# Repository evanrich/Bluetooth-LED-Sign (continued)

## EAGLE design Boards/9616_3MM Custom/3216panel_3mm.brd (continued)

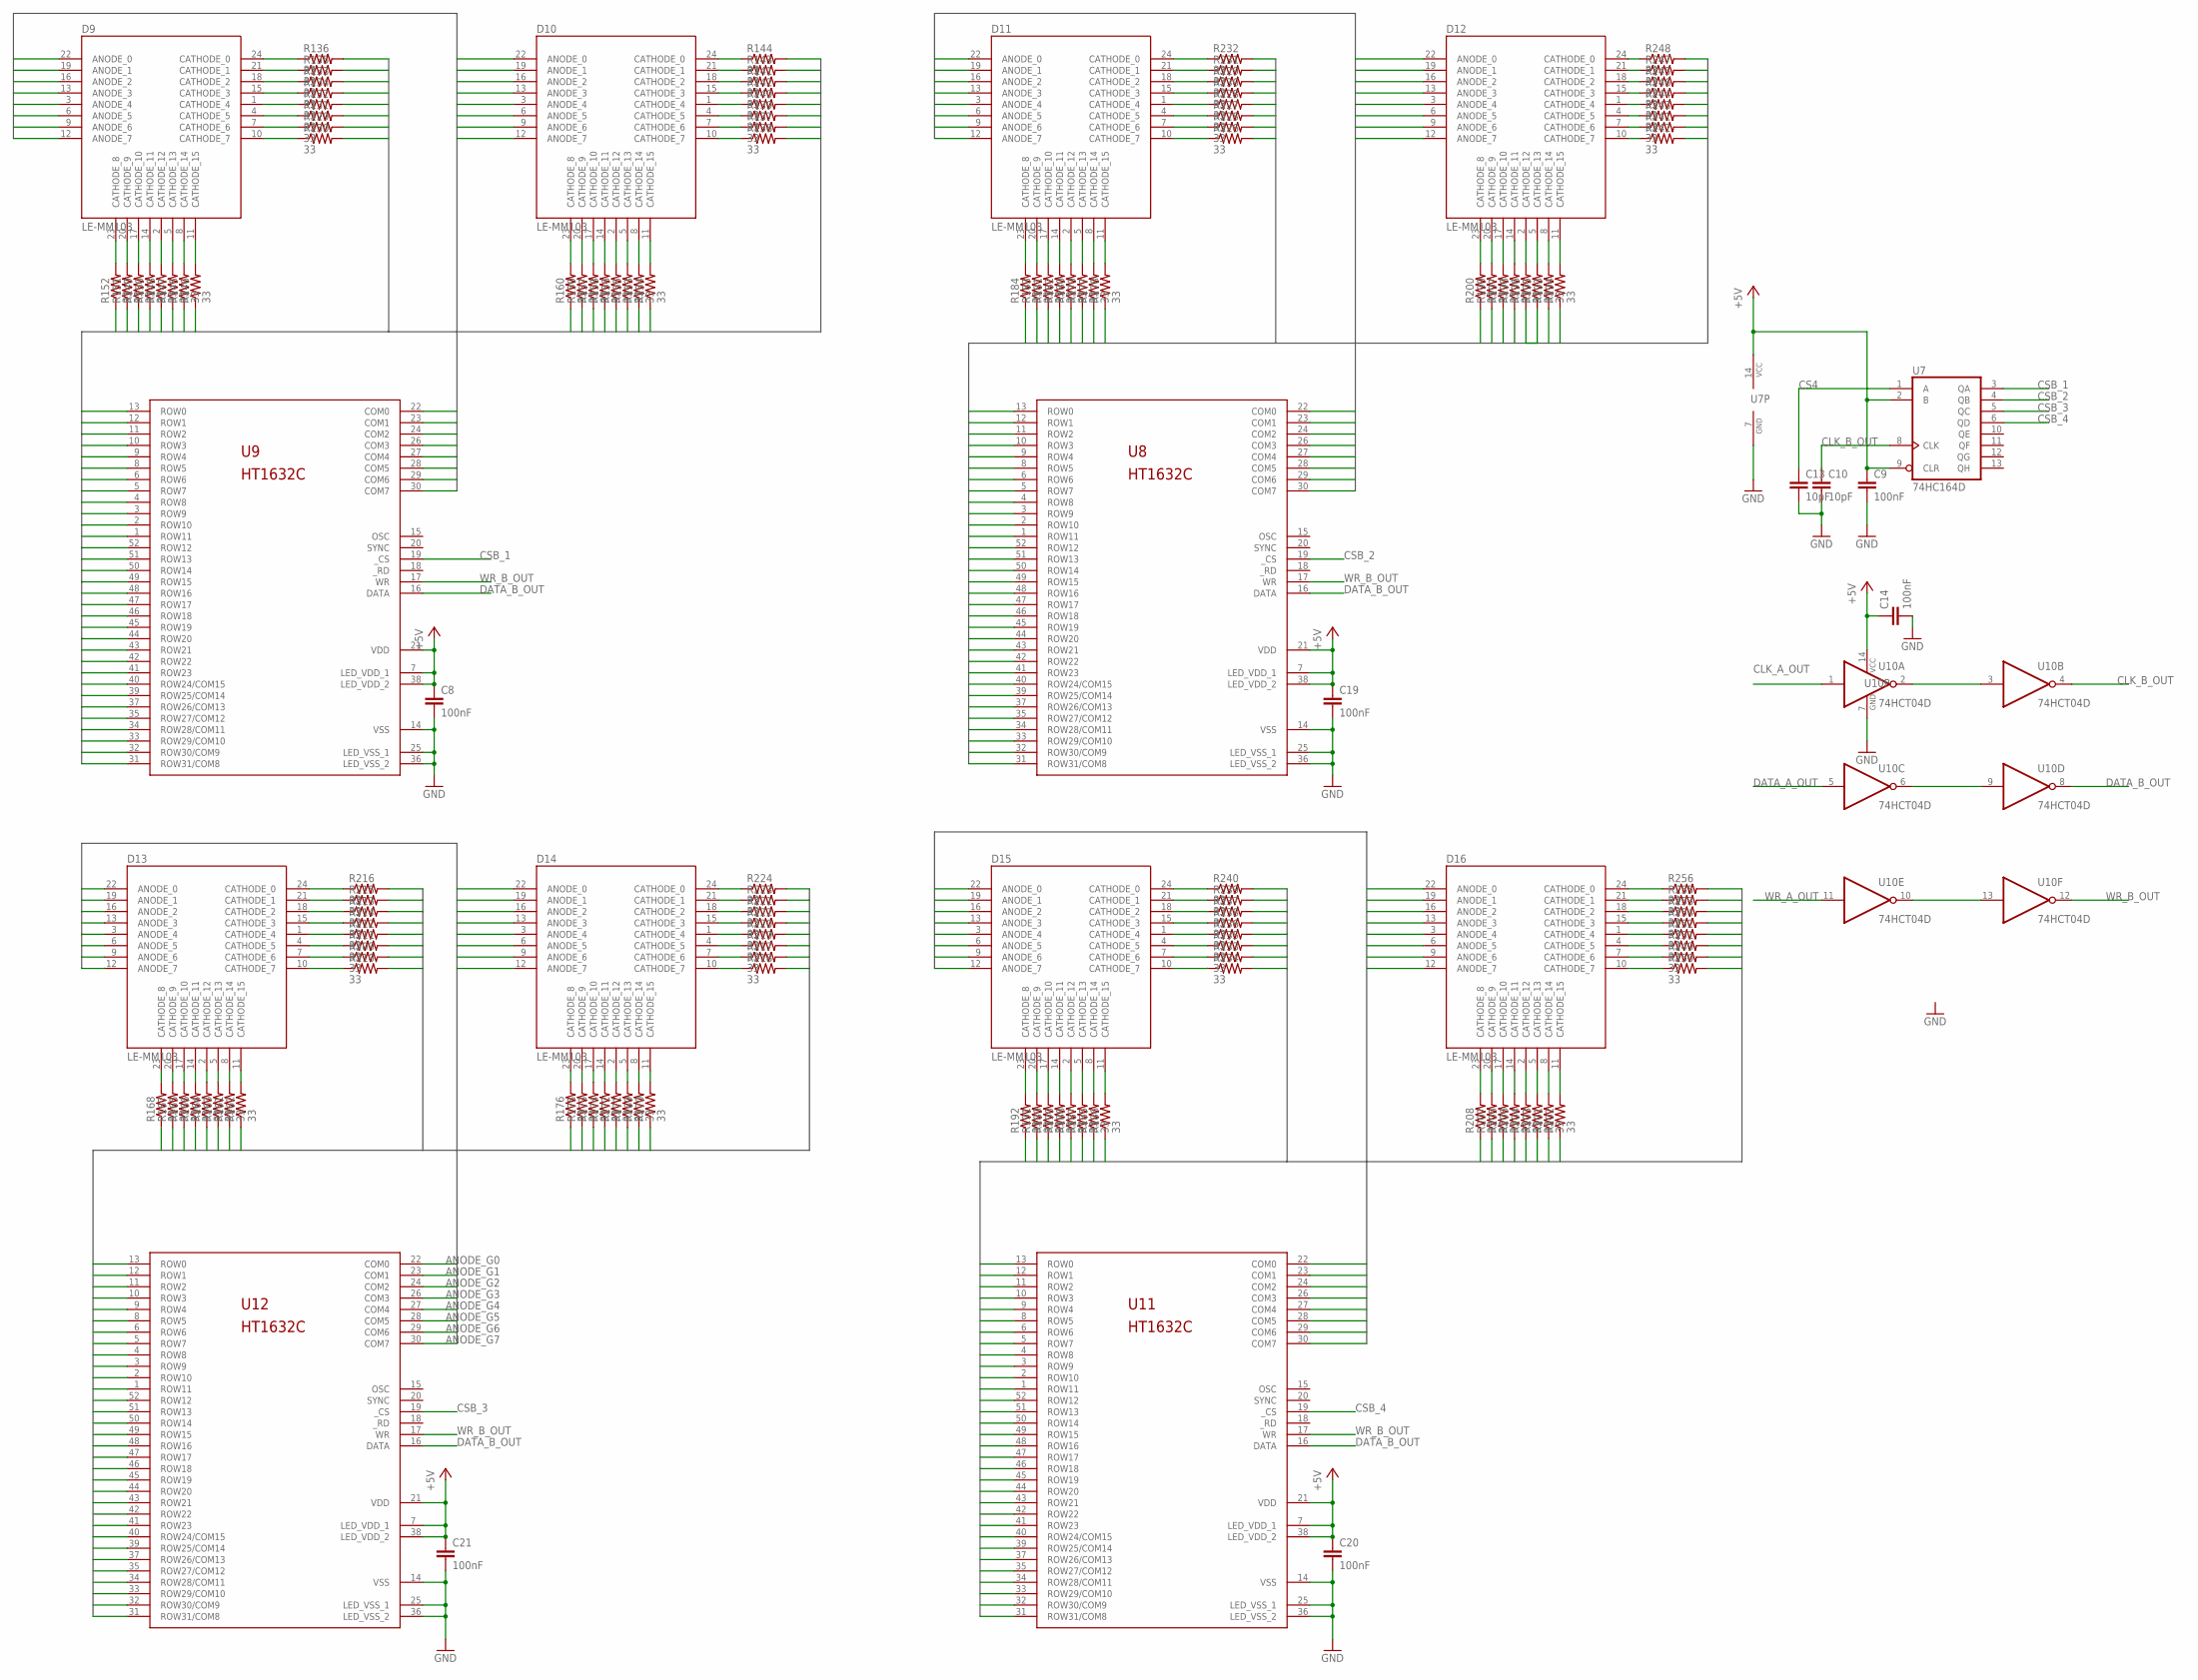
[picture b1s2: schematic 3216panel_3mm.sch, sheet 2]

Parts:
C8, C9, C14, C19, C20, C21: 100nF; 0805
C10, C13: 10pF; 0805
D9, D10, D11, D12, D13, D14, D15, D16: LE-MM103; 8X8_3MM_LED_MATRIX
R129, R130, R131, R132, R133, R134, R135, R136, R137, R138, R139, R140, R141, R142, R143, R144, R145, R146, R147, R148, R149, R150, R151, R152, R153, R154, R155, R156, R157, R158, R159, R160, R161, R162, R163, R164, R165, R166, R167, R168, R169, R170, R171, R172, R173, R174, R175, R176, R177, R178, R179, R180, R181, R182, R183, R184, R185, R186, R187, R188, R189, R190, R191, R192, R193, R194, R195, R196, R197, R198, R199, R200, R201, R202, R203, R204, R205, R206, R207, R208, R209, R210, R211, R212, R213, R214, R215, R216, R217, R218, R219, R220, R221, R222, R223, R224, R225, R226, R227, R228, R229, R230, R231, R232, R233, R234, R235, R236, R237, R238, R239, R240, R241, R242, R243, R244, R245, R246, R247, R248, R249, R250, R251, R252, R253, R254, R255, R256: 33; 0805
U7: 74HC164D; SO14
U8, U9, U11, U12: HT1632C; QFP52
U10: 74HCT04D; SO14

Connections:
+5V: C8.1, C9.1, C14.1, C19.1, C20.1, C21.1, U7.2 (B), U7.9 (CLR), U7.14 (VCC), U8.7 (LED_VDD_1), U8.21 (VDD), U8.38 (LED_VDD_2), U9.7 (LED_VDD_1), U9.21 (VDD), U9.38 (LED_VDD_2), U10.14 (VCC), U11.7 (LED_VDD_1), U11.21 (VDD), U11.38 (LED_VDD_2), U12.7 (LED_VDD_1), U12.21 (VDD), U12.38 (LED_VDD_2); also elsewhere on the board
ANODE_E0: D9.22 (ANODE_0), D10.22 (ANODE_0), U9.22 (COM0)
ANODE_E1: D9.19 (ANODE_1), D10.19 (ANODE_1), U9.23 (COM1)
ANODE_E2: D9.16 (ANODE_2), D10.16 (ANODE_2), U9.24 (COM2)
ANODE_E3: D9.13 (ANODE_3), D10.13 (ANODE_3), U9.26 (COM3)
ANODE_E4: D9.3 (ANODE_4), D10.3 (ANODE_4), U9.27 (COM4)
ANODE_E5: D9.6 (ANODE_5), D10.6 (ANODE_5), U9.28 (COM5)
ANODE_E6: D9.9 (ANODE_6), D10.9 (ANODE_6), U9.29 (COM6)
ANODE_E7: D9.12 (ANODE_7), D10.12 (ANODE_7), U9.30 (COM7)
ANODE_F0: D11.22 (ANODE_0), D12.22 (ANODE_0), U8.22 (COM0)
ANODE_F1: D11.19 (ANODE_1), D12.19 (ANODE_1), U8.23 (COM1)
ANODE_F2: D11.16 (ANODE_2), D12.16 (ANODE_2), U8.24 (COM2)
ANODE_F3: D11.13 (ANODE_3), D12.13 (ANODE_3), U8.26 (COM3)
ANODE_F4: D11.3 (ANODE_4), D12.3 (ANODE_4), U8.27 (COM4)
ANODE_F5: D11.6 (ANODE_5), D12.6 (ANODE_5), U8.28 (COM5)
ANODE_F6: D11.9 (ANODE_6), D12.9 (ANODE_6), U8.29 (COM6)
ANODE_F7: D11.12 (ANODE_7), D12.12 (ANODE_7), U8.30 (COM7)
ANODE_G0: D13.22 (ANODE_0), D14.22 (ANODE_0), U12.22 (COM0)
ANODE_G1: D13.19 (ANODE_1), D14.19 (ANODE_1), U12.23 (COM1)
ANODE_G2: D13.16 (ANODE_2), D14.16 (ANODE_2), U12.24 (COM2)
ANODE_G3: D13.13 (ANODE_3), D14.13 (ANODE_3), U12.26 (COM3)
ANODE_G4: D13.3 (ANODE_4), D14.3 (ANODE_4), U12.27 (COM4)
ANODE_G5: D13.6 (ANODE_5), D14.6 (ANODE_5), U12.28 (COM5)
ANODE_G6: D13.9 (ANODE_6), D14.9 (ANODE_6), U12.29 (COM6)
ANODE_G7: D13.12 (ANODE_7), D14.12 (ANODE_7), U12.30 (COM7)
ANODE_H0: D15.22 (ANODE_0), D16.22 (ANODE_0), U11.22 (COM0)
ANODE_H1: D15.19 (ANODE_1), D16.19 (ANODE_1), U11.23 (COM1)
ANODE_H2: D15.16 (ANODE_2), D16.16 (ANODE_2), U11.24 (COM2)
ANODE_H3: D15.13 (ANODE_3), D16.13 (ANODE_3), U11.26 (COM3)
ANODE_H4: D15.3 (ANODE_4), D16.3 (ANODE_4), U11.27 (COM4)
ANODE_H5: D15.6 (ANODE_5), D16.6 (ANODE_5), U11.28 (COM5)
ANODE_H6: D15.9 (ANODE_6), D16.9 (ANODE_6), U11.29 (COM6)
ANODE_H7: D15.12 (ANODE_7), D16.12 (ANODE_7), U11.30 (COM7)
CATHODE_E0: R136.2, U9.13 (ROW0)
CATHODE_E1: R135.2, U9.12 (ROW1)
CATHODE_E2: R133.2, U9.11 (ROW2)
CATHODE_E3: R134.2, U9.10 (ROW3)
CATHODE_E4: R132.2, U9.9 (ROW4)
CATHODE_E5: R131.2, U9.8 (ROW5)
CATHODE_E6: R129.2, U9.6 (ROW6)
CATHODE_E7: R130.2, U9.5 (ROW7)
CATHODE_E8: R144.2, U9.4 (ROW8)
CATHODE_E9: R143.2, U9.3 (ROW9)
CATHODE_E10: R141.2, U9.2 (ROW10)
CATHODE_E11: R142.2, U9.1 (ROW11)
CATHODE_E12: R140.2, U9.52 (ROW12)
CATHODE_E13: R139.2, U9.51 (ROW13)
CATHODE_E14: R137.2, U9.50 (ROW14)
CATHODE_E15: R138.2, U9.49 (ROW15)
CATHODE_E16: R152.1, U9.48 (ROW16)
CATHODE_E17: R151.1, U9.47 (ROW17)
CATHODE_E18: R149.1, U9.46 (ROW18)
CATHODE_E19: R150.1, U9.45 (ROW19)
CATHODE_E20: R148.1, U9.44 (ROW20)
CATHODE_E21: R147.1, U9.43 (ROW21)
CATHODE_E22: R145.1, U9.42 (ROW22)
CATHODE_E23: R146.1, U9.41 (ROW23)
CATHODE_E24: R160.1, U9.40 (ROW24/COM15)
CATHODE_E25: R159.1, U9.39 (ROW25/COM14)
CATHODE_E26: R157.1, U9.37 (ROW26/COM13)
CATHODE_E27: R158.1, U9.35 (ROW27/COM12)
CATHODE_E28: R156.1, U9.34 (ROW28/COM11)
CATHODE_E29: R155.1, U9.33 (ROW29/COM10)
CATHODE_E30: R153.1, U9.32 (ROW30/COM9)
CATHODE_E31: R154.1, U9.31 (ROW31/COM8)
CATHODE_F0: R232.2, U8.13 (ROW0)
CATHODE_F1: R231.2, U8.12 (ROW1)
CATHODE_F2: R229.2, U8.11 (ROW2)
CATHODE_F3: R230.2, U8.10 (ROW3)
CATHODE_F4: R228.2, U8.9 (ROW4)
CATHODE_F5: R227.2, U8.8 (ROW5)
CATHODE_F6: R225.2, U8.6 (ROW6)
CATHODE_F7: R226.2, U8.5 (ROW7)
CATHODE_F8: R248.2, U8.4 (ROW8)
CATHODE_F9: R247.2, U8.3 (ROW9)
CATHODE_F10: R245.2, U8.2 (ROW10)
CATHODE_F11: R246.2, U8.1 (ROW11)
CATHODE_F12: R244.2, U8.52 (ROW12)
CATHODE_F13: R243.2, U8.51 (ROW13)
CATHODE_F14: R241.2, U8.50 (ROW14)
CATHODE_F15: R242.2, U8.49 (ROW15)
CATHODE_F16: R184.1, U8.48 (ROW16)
CATHODE_F17: R183.1, U8.47 (ROW17)
CATHODE_F18: R181.1, U8.46 (ROW18)
CATHODE_F19: R182.1, U8.45 (ROW19)
CATHODE_F20: R180.1, U8.44 (ROW20)
CATHODE_F21: R179.1, U8.43 (ROW21)
CATHODE_F22: R177.1, U8.42 (ROW22)
CATHODE_F23: R178.1, U8.41 (ROW23)
CATHODE_F24: R200.1, U8.40 (ROW24/COM15)
CATHODE_F25: R199.1, U8.39 (ROW25/COM14)
CATHODE_F26: R197.1, U8.37 (ROW26/COM13)
CATHODE_F27: R198.1, U8.35 (ROW27/COM12)
CATHODE_F28: R196.1, U8.34 (ROW28/COM11)
CATHODE_F29: R195.1, U8.33 (ROW29/COM10)
CATHODE_F30: R193.1, U8.32 (ROW30/COM9)
CATHODE_F31: R194.1, U8.31 (ROW31/COM8)
CATHODE_G0: R216.2, U12.13 (ROW0)
CATHODE_G1: R215.2, U12.12 (ROW1)
CATHODE_G2: R213.2, U12.11 (ROW2)
CATHODE_G3: R214.2, U12.10 (ROW3)
CATHODE_G4: R212.2, U12.9 (ROW4)
CATHODE_G5: R211.2, U12.8 (ROW5)
CATHODE_G6: R209.2, U12.6 (ROW6)
CATHODE_G7: R210.2, U12.5 (ROW7)
CATHODE_G8: R224.2, U12.4 (ROW8)
CATHODE_G9: R223.2, U12.3 (ROW9)
CATHODE_G10: R221.2, U12.2 (ROW10)
CATHODE_G11: R222.2, U12.1 (ROW11)
CATHODE_G12: R220.2, U12.52 (ROW12)
CATHODE_G13: R219.2, U12.51 (ROW13)
CATHODE_G14: R217.2, U12.50 (ROW14)
CATHODE_G15: R218.2, U12.49 (ROW15)
CATHODE_G16: R168.1, U12.48 (ROW16)
CATHODE_G17: R167.1, U12.47 (ROW17)
CATHODE_G18: R165.1, U12.46 (ROW18)
CATHODE_G19: R166.1, U12.45 (ROW19)
CATHODE_G20: R164.1, U12.44 (ROW20)
CATHODE_G21: R163.1, U12.43 (ROW21)
CATHODE_G22: R161.1, U12.42 (ROW22)
CATHODE_G23: R162.1, U12.41 (ROW23)
CATHODE_G24: R176.1, U12.40 (ROW24/COM15)
CATHODE_G25: R175.1, U12.39 (ROW25/COM14)
CATHODE_G26: R173.1, U12.37 (ROW26/COM13)
CATHODE_G27: R174.1, U12.35 (ROW27/COM12)
CATHODE_G28: R172.1, U12.34 (ROW28/COM11)
CATHODE_G29: R171.1, U12.33 (ROW29/COM10)
CATHODE_G30: R169.1, U12.32 (ROW30/COM9)
CATHODE_G31: R170.1, U12.31 (ROW31/COM8)
CATHODE_H0: R240.2, U11.13 (ROW0)
CATHODE_H1: R239.2, U11.12 (ROW1)
CATHODE_H2: R237.2, U11.11 (ROW2)
CATHODE_H3: R238.2, U11.10 (ROW3)
CATHODE_H4: R236.2, U11.9 (ROW4)
CATHODE_H5: R235.2, U11.8 (ROW5)
CATHODE_H6: R233.2, U11.6 (ROW6)
CATHODE_H7: R234.2, U11.5 (ROW7)
CATHODE_H8: R256.2, U11.4 (ROW8)
CATHODE_H9: R255.2, U11.3 (ROW9)
CATHODE_H10: R253.2, U11.2 (ROW10)
CATHODE_H11: R254.2, U11.1 (ROW11)
CATHODE_H12: R252.2, U11.52 (ROW12)
CATHODE_H13: R251.2, U11.51 (ROW13)
CATHODE_H14: R249.2, U11.50 (ROW14)
CATHODE_H15: R250.2, U11.49 (ROW15)
CATHODE_H16: R192.1, U11.48 (ROW16)
CATHODE_H17: R191.1, U11.47 (ROW17)
CATHODE_H18: R189.1, U11.46 (ROW18)
CATHODE_H19: R190.1, U11.45 (ROW19)
CATHODE_H20: R188.1, U11.44 (ROW20)
CATHODE_H21: R187.1, U11.43 (ROW21)
CATHODE_H22: R185.1, U11.42 (ROW22)
CATHODE_H23: R186.1, U11.41 (ROW23)
CATHODE_H24: R208.1, U11.40 (ROW24/COM15)
CATHODE_H25: R207.1, U11.39 (ROW25/COM14)
CATHODE_H26: R205.1, U11.37 (ROW26/COM13)
CATHODE_H27: R206.1, U11.35 (ROW27/COM12)
CATHODE_H28: R204.1, U11.34 (ROW28/COM11)
CATHODE_H29: R203.1, U11.33 (ROW29/COM10)
CATHODE_H30: R201.1, U11.32 (ROW30/COM9)
CATHODE_H31: R202.1, U11.31 (ROW31/COM8)
CLK_A_OUT: U10.1 (I); also elsewhere on the board
CLK_B_OUT: C10.1, U7.8 (CLK), U10.4 (O); also elsewhere on the board
CS4: C13.1, U7.1 (A); also elsewhere on the board
CSB_1: U7.3 (QA), U9.19 (_CS)
CSB_2: U7.4 (QB), U8.19 (_CS)
CSB_3: U7.5 (QC), U12.19 (_CS)
CSB_4: U7.6 (QD), U11.19 (_CS); also elsewhere on the board
DATA_A_OUT: U10.5 (I); also elsewhere on the board
DATA_B_OUT: U8.16 (DATA), U9.16 (DATA), U10.8 (O), U11.16 (DATA), U12.16 (DATA); also elsewhere on the board
GND: C8.2, C9.2, C10.2, C13.2, C14.2, C19.2, C20.2, C21.2, U7.7 (GND), U8.14 (VSS), U8.25 (LED_VSS_1), U8.36 (LED_VSS_2), U9.14 (VSS), U9.25 (LED_VSS_1), U9.36 (LED_VSS_2), U10.7 (GND), U11.14 (VSS), U11.25 (LED_VSS_1), U11.36 (LED_VSS_2), U12.14 (VSS), U12.25 (LED_VSS_1), U12.36 (LED_VSS_2); also elsewhere on the board
unnamed: D9.7 (CATHODE_6), R129.1
unnamed: D9.10 (CATHODE_7), R130.1
unnamed: D9.4 (CATHODE_5), R131.1
unnamed: D9.1 (CATHODE_4), R132.1
unnamed: D9.18 (CATHODE_2), R133.1
unnamed: D9.15 (CATHODE_3), R134.1
unnamed: D9.21 (CATHODE_1), R135.1
unnamed: D9.24 (CATHODE_0), R136.1
unnamed: D10.7 (CATHODE_6), R137.1
unnamed: D10.10 (CATHODE_7), R138.1
unnamed: D10.4 (CATHODE_5), R139.1
unnamed: D10.1 (CATHODE_4), R140.1
unnamed: D10.18 (CATHODE_2), R141.1
unnamed: D10.15 (CATHODE_3), R142.1
unnamed: D10.21 (CATHODE_1), R143.1
unnamed: D10.24 (CATHODE_0), R144.1
unnamed: D9.8 (CATHODE_14), R145.2
unnamed: D9.11 (CATHODE_15), R146.2
unnamed: D9.5 (CATHODE_13), R147.2
unnamed: D9.2 (CATHODE_12), R148.2
unnamed: D9.17 (CATHODE_10), R149.2
unnamed: D9.14 (CATHODE_11), R150.2
unnamed: D9.20 (CATHODE_9), R151.2
unnamed: D9.23 (CATHODE_8), R152.2
unnamed: D10.8 (CATHODE_14), R153.2
unnamed: D10.11 (CATHODE_15), R154.2
unnamed: D10.5 (CATHODE_13), R155.2
unnamed: D10.2 (CATHODE_12), R156.2
unnamed: D10.17 (CATHODE_10), R157.2
unnamed: D10.14 (CATHODE_11), R158.2
unnamed: D10.20 (CATHODE_9), R159.2
unnamed: D10.23 (CATHODE_8), R160.2
unnamed: U10.2 (O), U10.3 (I)
unnamed: U10.6 (O), U10.9 (I)
unnamed: U10.10 (O), U10.13 (I)
unnamed: D13.7 (CATHODE_6), R209.1
unnamed: D13.10 (CATHODE_7), R210.1
unnamed: D13.4 (CATHODE_5), R211.1
unnamed: D13.1 (CATHODE_4), R212.1
unnamed: D13.18 (CATHODE_2), R213.1
unnamed: D13.15 (CATHODE_3), R214.1
unnamed: D13.21 (CATHODE_1), R215.1
unnamed: D13.24 (CATHODE_0), R216.1
unnamed: D13.8 (CATHODE_14), R161.2
unnamed: D13.11 (CATHODE_15), R162.2
unnamed: D13.5 (CATHODE_13), R163.2
unnamed: D13.2 (CATHODE_12), R164.2
unnamed: D13.17 (CATHODE_10), R165.2
unnamed: D13.14 (CATHODE_11), R166.2
unnamed: D13.20 (CATHODE_9), R167.2
unnamed: D13.23 (CATHODE_8), R168.2
unnamed: D14.8 (CATHODE_14), R169.2
unnamed: D14.11 (CATHODE_15), R170.2
unnamed: D14.5 (CATHODE_13), R171.2
unnamed: D14.2 (CATHODE_12), R172.2
unnamed: D14.17 (CATHODE_10), R173.2
unnamed: D14.14 (CATHODE_11), R174.2
unnamed: D14.20 (CATHODE_9), R175.2
unnamed: D14.23 (CATHODE_8), R176.2
unnamed: D14.7 (CATHODE_6), R217.1
unnamed: D14.10 (CATHODE_7), R218.1
unnamed: D14.4 (CATHODE_5), R219.1
unnamed: D14.1 (CATHODE_4), R220.1
unnamed: D14.18 (CATHODE_2), R221.1
unnamed: D14.15 (CATHODE_3), R222.1
unnamed: D14.21 (CATHODE_1), R223.1
unnamed: D14.24 (CATHODE_0), R224.1
unnamed: D15.8 (CATHODE_14), R185.2
unnamed: D15.11 (CATHODE_15), R186.2
unnamed: D15.5 (CATHODE_13), R187.2
unnamed: D15.2 (CATHODE_12), R188.2
unnamed: D15.17 (CATHODE_10), R189.2
unnamed: D15.14 (CATHODE_11), R190.2
unnamed: D15.20 (CATHODE_9), R191.2
unnamed: D15.23 (CATHODE_8), R192.2
unnamed: D15.7 (CATHODE_6), R233.1
unnamed: D15.10 (CATHODE_7), R234.1
unnamed: D15.4 (CATHODE_5), R235.1
unnamed: D15.1 (CATHODE_4), R236.1
unnamed: D15.18 (CATHODE_2), R237.1
unnamed: D15.15 (CATHODE_3), R238.1
unnamed: D15.21 (CATHODE_1), R239.1
unnamed: D15.24 (CATHODE_0), R240.1
unnamed: D16.8 (CATHODE_14), R201.2
unnamed: D16.11 (CATHODE_15), R202.2
unnamed: D16.5 (CATHODE_13), R203.2
unnamed: D16.2 (CATHODE_12), R204.2
unnamed: D16.17 (CATHODE_10), R205.2
unnamed: D16.14 (CATHODE_11), R206.2
unnamed: D16.20 (CATHODE_9), R207.2
unnamed: D16.23 (CATHODE_8), R208.2
unnamed: D16.7 (CATHODE_6), R249.1
unnamed: D16.10 (CATHODE_7), R250.1
unnamed: D16.4 (CATHODE_5), R251.1
unnamed: D16.1 (CATHODE_4), R252.1
unnamed: D16.18 (CATHODE_2), R253.1
unnamed: D16.15 (CATHODE_3), R254.1
unnamed: D16.21 (CATHODE_1), R255.1
unnamed: D16.24 (CATHODE_0), R256.1
unnamed: D12.8 (CATHODE_14), R193.2
unnamed: D12.11 (CATHODE_15), R194.2
unnamed: D12.5 (CATHODE_13), R195.2
unnamed: D12.2 (CATHODE_12), R196.2
unnamed: D12.17 (CATHODE_10), R197.2
unnamed: D12.14 (CATHODE_11), R198.2
unnamed: D12.20 (CATHODE_9), R199.2
unnamed: D12.23 (CATHODE_8), R200.2
unnamed: D12.7 (CATHODE_6), R241.1
unnamed: D12.10 (CATHODE_7), R242.1
unnamed: D12.4 (CATHODE_5), R243.1
unnamed: D12.1 (CATHODE_4), R244.1
unnamed: D12.18 (CATHODE_2), R245.1
unnamed: D12.15 (CATHODE_3), R246.1
unnamed: D12.21 (CATHODE_1), R247.1
unnamed: D12.24 (CATHODE_0), R248.1
unnamed: D11.8 (CATHODE_14), R177.2
unnamed: D11.11 (CATHODE_15), R178.2
unnamed: D11.5 (CATHODE_13), R179.2
unnamed: D11.2 (CATHODE_12), R180.2
unnamed: D11.17 (CATHODE_10), R181.2
unnamed: D11.14 (CATHODE_11), R182.2
unnamed: D11.20 (CATHODE_9), R183.2
unnamed: D11.23 (CATHODE_8), R184.2
unnamed: D11.7 (CATHODE_6), R225.1
unnamed: D11.10 (CATHODE_7), R226.1
unnamed: D11.4 (CATHODE_5), R227.1
unnamed: D11.1 (CATHODE_4), R228.1
unnamed: D11.18 (CATHODE_2), R229.1
unnamed: D11.15 (CATHODE_3), R230.1
unnamed: D11.21 (CATHODE_1), R231.1
unnamed: D11.24 (CATHODE_0), R232.1
WR_A_OUT: U10.11 (I); also elsewhere on the board
WR_B_OUT: U8.17 (WR), U9.17 (WR), U10.12 (O), U11.17 (WR), U12.17 (WR); also elsewhere on the board
